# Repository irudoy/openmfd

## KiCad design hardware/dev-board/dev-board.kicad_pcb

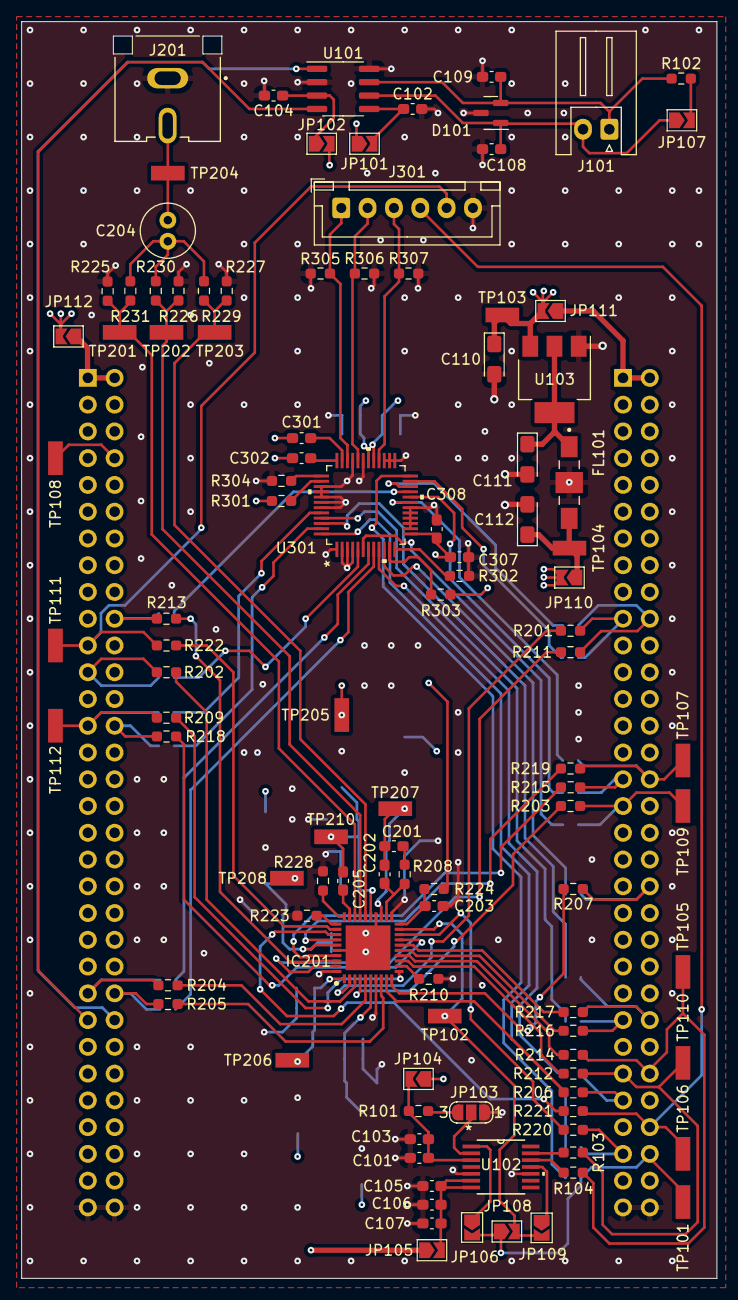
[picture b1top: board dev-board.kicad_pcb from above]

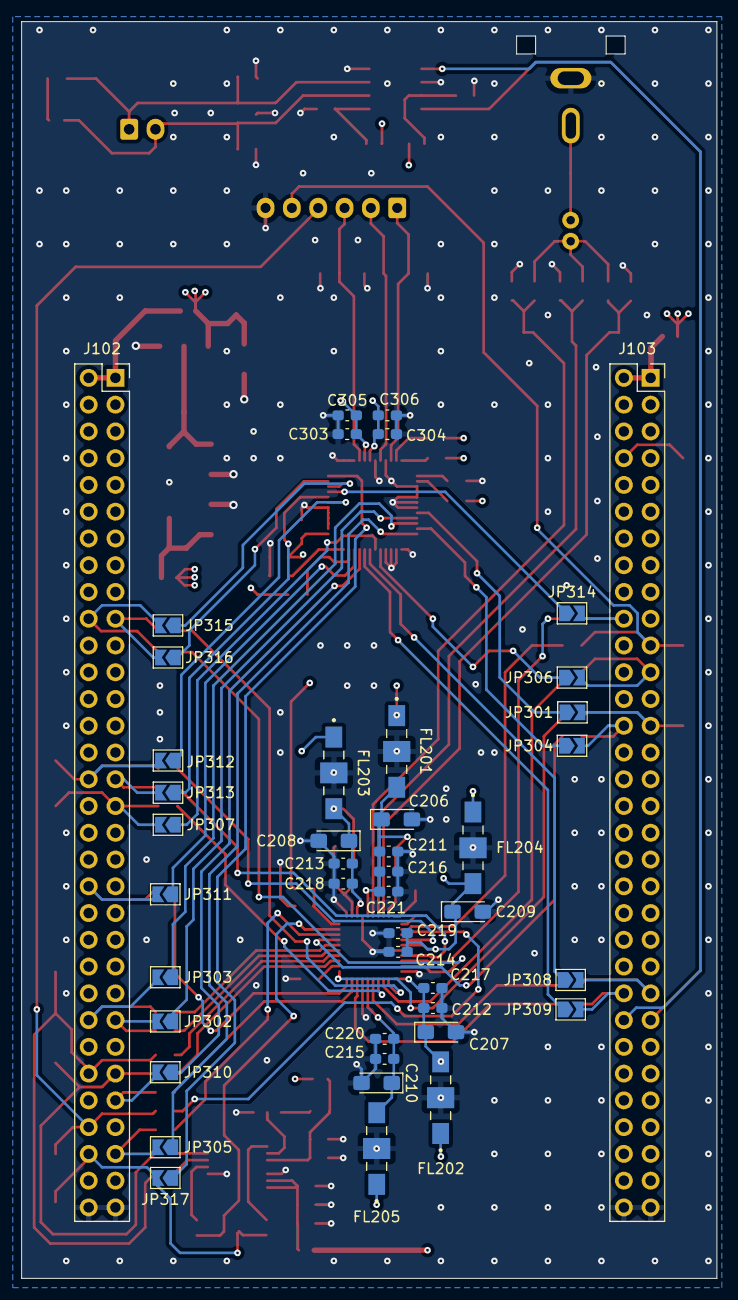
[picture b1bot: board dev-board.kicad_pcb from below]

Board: 4 copper layers, 66.0 x 119.3 mm, 150 parts (44 on the bottom side), 109 nets.

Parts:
C101, C102, C104, C105, C106, C203, C211, C212, C213, C214, C215: 100n; C_0603_1608Metric_Pad1.08x0.95mm_HandSolder
C103, C107, C221: 1u; C_0603_1608Metric_Pad1.08x0.95mm_HandSolder
C108, C109: 47p; C_0603_1608Metric_Pad1.08x0.95mm_HandSolder
C110: 10u; CP_EIA-3216-18_Kemet-A_Pad1.58x1.35mm_HandSolder
C111: 22u; CP_EIA-3216-18_Kemet-A_Pad1.58x1.35mm_HandSolder
C112, C206, C207, C208, C209, C210: 33u; CP_EIA-3216-18_Kemet-A_Pad1.58x1.35mm_HandSolder
C201: 150n; C_0603_1608Metric_Pad1.08x0.95mm_HandSolder
C202: 12n; C_0603_1608Metric_Pad1.08x0.95mm_HandSolder
C204: 220uf; C_Radial_D5.0mm_H11.0mm_P2.00mm
C205: 2n2; C_0603_1608Metric_Pad1.08x0.95mm_HandSolder
C216, C217, C218, C219, C220: 10n; C_0603_1608Metric_Pad1.08x0.95mm_HandSolder
C301, C302, C303, C304, C307: 100nf; C_0603_1608Metric_Pad1.08x0.95mm_HandSolder
C305, C306, C308: 10nf; C_0603_1608Metric_Pad1.08x0.95mm_HandSolder
D101: ESDCAN24-2BLY; SOT-23
FL101, FL201, FL202, FL203, FL204, FL205: Filter_EMI_LCL; FIL_NFE61PT472C1H9L
IC201: ADV7393BCPZ; QFN50P600X600X80-41N
J101: Conn_01x02_Pin; JST_XH_S2B-XH-A_1x02_P2.50mm_Horizontal
J102: DISC1-P1; PinSocket_2x32_P2.54mm_Vertical
J103: DISC1-P2; PinSocket_2x32_P2.54mm_Vertical
J201: CVBS; CUI_RCJ-044
J301: Connector RGB; JST_XH_B6B-XH-A_1x06_P2.50mm_Vertical
JP101, JP102, JP104, JP105, JP106, JP107, JP108, JP109, JP110, JP111, JP112, JP301, JP302, JP303, JP304, JP305, JP306, JP307, JP308, JP309, JP310, JP311, JP312, JP313, JP314, JP315, JP316, JP317: SolderJumper_2_Open; SolderJumper-2_P1.3mm_Open_TrianglePad1.0x1.5mm
JP103: SolderJumper_3_Open; SolderJumper-3_P1.3mm_Open_RoundedPad1.0x1.5mm_NumberLabels
R101, R223, R229, R230, R231: 0Ω; R_0603_1608Metric_Pad0.98x0.95mm_HandSolder
R102: 120; R_0603_1608Metric_Pad0.98x0.95mm_HandSolder
R103, R104, R201, R202, R203, R204, R205, R206, R207, R209, R210, R211, R212, R213, R214, R215, R216, R217, R218, R219, R220, R221, R222: 0; R_0603_1608Metric_Pad0.98x0.95mm_HandSolder
R208: 170 (169); R_0603_1608Metric_Pad0.98x0.95mm_HandSolder
R224: 10K; R_0603_1608Metric_Pad0.98x0.95mm_HandSolder
R225, R226, R227, R305, R306, R307: 75; R_0603_1608Metric_Pad0.98x0.95mm_HandSolder
R228: 510 1%; R_0603_1608Metric_Pad0.98x0.95mm_HandSolder
R301, R303: 4K7; R_0603_1608Metric_Pad0.98x0.95mm_HandSolder
R302: 1K; R_0603_1608Metric_Pad0.98x0.95mm_HandSolder
R304: 560; R_0603_1608Metric_Pad0.98x0.95mm_HandSolder
TP101, TP102, TP103, TP104, TP105, TP106, TP107, TP108, TP109, TP110, TP111, TP112, TP201, TP202, TP203, TP204, TP205, TP206, TP207, TP208, TP210: TestPoint_Flag; KEYSTONE_5015
U101: MCP2562-E-SN; SOIC-8_3.9x4.9mm_P1.27mm
U102: CDCE913PW; PW14
U103: AMS1117-1.8; SOT-223-3_TabPin2
U301: ADV7125KSTZ140

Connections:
+1V8: FL203.1, FL204.1, FL205.1, JP104.1 (A), JP110.2 (B)
+1V8_I: C101.1, C103.1, JP104.2 (B), R101.1, U102.3 (VDD)
+3V3: FL201.1, FL202.1, JP101.1 (A), JP105.1 (A), JP112.2 (B), R224.2, TP205.1
+3V3_C: C102.1, JP101.2 (B), U101.5 (Vio)
+3V3_I: C105.1, C106.1, C107.1, JP105.2 (B), U102.6 (VDDOUT), U102.7 (VDDOUT)
+3V3_IN: J103.1 (3V3), J103.2 (3V3), JP112.1 (A)
+5V: C110.1, C301.2, C302.2, C303.2, C304.2, C305.2, C306.2, C307.2, C308.2, JP102.2 (B), JP111.2 (B), R301.2, R303.2, TP103.1, U103.3 (VI), U301.13 (VAA), U301.29 (VAA), U301.30 (VAA)
+5V_C: C104.1, JP102.1 (A), U101.3 (VDD)
+5V_IN: J102.1 (5V), J102.2 (5V), JP111.1 (A)
/CANH: C109.1, D101.2 (K), J101.1, R102.1, U101.7 (CANH)
/CANL: C108.2, D101.1 (K), J101.2, JP107.1 (A), U101.6 (CANL)
ADV7_B3: JP312.1 (A), U301.19 (B3)
ADV7_B4: JP313.1 (A), U301.20 (B4)
ADV7_B5: JP314.1 (A), U301.21 (B5)
ADV7_B6: JP315.1 (A), U301.22 (B6)
ADV7_B7: JP316.1 (A), U301.23 (B7)
ADV7_CLK: JP317.1 (A), U301.24 (CLOCK)
ADV7_G2: JP306.1 (A), U301.5 (G2)
ADV7_G3: JP307.1 (A), U301.6 (G3)
ADV7_G4: JP308.1 (A), U301.7 (G4)
ADV7_G5: JP309.1 (A), U301.8 (G5)
ADV7_G6: JP310.1 (A), U301.9 (G6)
ADV7_G7: JP311.1 (A), U301.10 (G7)
ADV7_IOB: J301.3, R307.1, U301.28 (IOB)
ADV7_IOG: J301.2, R306.1, U301.32 (IOG)
ADV7_IOR: J301.1, R305.1, U301.34 (IOR)
ADV7_R3: JP301.1 (A), U301.44 (R3)
ADV7_R4: JP302.1 (A), U301.45 (R4)
ADV7_R5: JP303.1 (A), U301.46 (R5)
ADV7_R6: JP304.1 (A), U301.47 (R6)
ADV7_R7: JP305.1 (A), U301.48 (R7)
ADV_CLKIN: IC201.19 (CLKIN), JP108.2 (B), JP109.2 (B), TP102.1
ADV_COMP: C205.2, IC201.29 (COMP)
ADV_RSET: IC201.30 (RSET), R228.2
AVDD_3V3: C205.1, C206.1, C211.1, C216.1, C221.1, FL201.3, IC201.25 (VAA), TP210.1
CAN_RX: J103.49 (PB12), U101.4 (RXD)
CAN_TX: J103.50 (PB13), U101.1 (TXD)
DAC_1: IC201.28 (DAC_1), R225.2, R231.2, TP201.1
DAC_2: IC201.27 (DAC_2), R226.2, R230.2, TP202.1
DAC_3: IC201.26 (DAC_3), R227.2, R229.2, TP203.1
DVDD_1V8_1: C210.1, C215.1, C220.1, FL205.3, IC201.6 (VDD_1)
DVDD_1V8_2: C209.1, C214.1, C219.1, FL204.3, IC201.35 (VDD_2), TP208.1
DVDD_IO_3V3: C207.1, C212.1, C217.1, FL202.3, IC201.1 (VDD_IO), TP206.1
EXT_LF: C202.2, IC201.22 (EXT_LF), R208.1
GND: C101.2, C102.2, C103.2, C104.2, C105.2, C106.2, C107.2, C108.1, C109.2, C110.2, C111.2, C112.2, C203.2, C206.2, C207.2, C208.2, C209.2, C210.2, C211.2, C212.2, C213.2, C214.2, C215.2, C216.2, C217.2, C218.2, C219.2, C220.2, C221.2, C303.1, C304.1, C305.1, C306.1, C307.1, C308.1, D101.3 (A), FL101.2, FL201.2, FL202.2, FL203.2, FL204.2, FL205.2, IC201.7 (DGND_1), IC201.21 (PGND), IC201.24 (AGND_1), IC201.36 (DGND_2), IC201.40 (GND_IO), IC201.41 (AGND_2), J102.63 (GND), J102.64 (GND), J103.63 (GND), J103.64 (GND), J201.2 (Ext), J301.6, JP103.1 (A), R210.1, R223.1, R225.1, R226.1, R227.1, R228.1, R302.2, R304.2, R305.2, R306.2, R307.2, U101.2 (VSS), U101.8 (STBY), U102.5 (GND), U102.10 (GND), U103.1 (GND), U301.1 (GND), U301.2 (GND), U301.3 (G0), U301.4 (G1), U301.14 (GND), U301.15 (GND), U301.16 (B0), U301.17 (B1), U301.18 (B2), U301.25 (GND), U301.26 (GND), U301.27 (IOB*), U301.31 (IOG*), U301.33 (IOR*), U301.39 (GND), U301.40 (GND), U301.41 (R0), U301.42 (R1), U301.43 (R2)
I2C_SCL: J102.54 (PA8), R104.1, R214.1, TP105.1
I2C_SDA: J102.53 (PC9), R103.1, R212.1, TP110.1
LTDC_B3: J102.32 (PG11), JP312.2 (B), R219.2, TP107.1
LTDC_B4: J102.31 (PG12), JP313.2 (B), R215.2
LTDC_B5: J103.20 (PA3), JP314.2 (B), R213.2
LTDC_B6: J102.20 (PB8), JP315.2 (B), R211.2
LTDC_B7: J102.19 (PB9), JP316.2 (B), R201.1
LTDC_CLK: J102.60 (PG7), JP106.2 (B), JP108.1 (A), JP317.2 (B), TP101.1
LTDC_DE: J103.8 (PF10), TP108.1
LTDC_G2: J103.23 (PA6), JP306.2 (B), R202.1
LTDC_G3: J102.33 (PG10), JP307.2 (B), R203.1, TP109.1
LTDC_G4: J103.47 (PB10), JP308.2 (B), R204.1
LTDC_G5: J103.48 (PB11), JP309.2 (B), R205.1
LTDC_G6: J102.55 (PC7), JP310.2 (B), R206.1
LTDC_G7: J102.40 (PD3), JP311.2 (B), R207.1
LTDC_HSYNC: J102.58 (PC6), J301.4, R221.2, TP106.1
LTDC_R3: J103.27 (PB0), JP301.2 (B), R209.1, TP112.1
LTDC_R4: J102.49 (PA11), JP302.2 (B), R216.1
LTDC_R5: J102.50 (PA12), JP303.2 (B), R217.1
LTDC_R6: J103.28 (PB1), JP304.2 (B), R218.1
LTDC_R7: J102.59 (PG6), JP305.2 (B), R220.1
LTDC_VSYNC: J103.21 (PA4), J301.5, R222.2, TP111.1
unnamed: C201.2, R208.2
unnamed: C204.1, R229.1, R230.1, R231.1
unnamed: IC201.12 (ALSB), R210.2
unnamed: IC201.34 (P0), R219.1
unnamed: IC201.37 (P1), R215.1
unnamed: IC201.38 (P2), R213.1
unnamed: IC201.39 (P3), R211.1
unnamed: IC201.2 (P4), R201.2
unnamed: IC201.3 (P5), R202.2
unnamed: IC201.4 (P6), R203.2
unnamed: IC201.5 (P7), R204.2
unnamed: IC201.8, R205.2
unnamed: IC201.9, R206.2
unnamed: IC201.10, R207.2
unnamed: IC201.11, R209.2
unnamed: IC201.15 (P12), R216.2
unnamed: IC201.16 (P13), R217.2
unnamed: IC201.17 (P14), R218.2
unnamed: IC201.18 (P15), R220.2
unnamed: IC201.14 (SCL), R214.2
unnamed: IC201.13 (SDA), R212.2
unnamed: IC201.33 (~HSYNC), R221.1
unnamed: C203.1, IC201.20 (~RESET), R224.1
unnamed: IC201.32 (~VSYNC), R222.1
unnamed: C204.2, J201.1 (In), TP204.1
unnamed: JP103.3 (B), R101.2
unnamed: JP103.2 (C), U102.2 (S0)
unnamed: JP106.1 (A), U102.1 (XIN/CLK)
unnamed: JP107.2 (B), R102.2
unnamed: JP109.1 (A), U102.11 (Y1)
unnamed: C112.1, FL101.3, JP110.1 (A), TP104.1
unnamed: R103.2, U102.13 (S1/SDA)
unnamed: R104.2, U102.12 (S2/SCL)
unnamed: C111.1, FL101.1, U103.2 (VO)
unnamed: R303.1, U301.11 (BLANK*)
unnamed: C301.1, U301.35 (COMP)
unnamed: R301.1, U301.38 (PSAVE*)
unnamed: R304.1, U301.37 (RSET)
unnamed: R302.1, U301.12 (SYNC*)
unnamed: C302.1, U301.36 (VREF)
PVDD_1V8: C201.1, C202.1, C208.1, C213.1, C218.1, FL203.3, IC201.23 (PVDD), TP207.1
SFL: IC201.31 (SFL), R223.2

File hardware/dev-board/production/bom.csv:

Designator,Footprint,Quantity,Value,LCSC Part #
"C101, C102, C104, C105, C106, C203, C211, C212, C213, C214, C215",0603,11,100n,C14663
"C103, C107, C221",0603,3,1u,C14663
"C108, C109",0603,2,47p,C94904
C110,CP_EIA-3216-18_Kemet-A_Pad1.58x1.35mm_HandSolder,1,10u,
C111,CP_EIA-3216-18_Kemet-A_Pad1.58x1.35mm_HandSolder,1,22u,
"C112, C206, C207, C208, C209, C210",CP_EIA-3216-18_Kemet-A_Pad1.58x1.35mm_HandSolder,6,33u,
C201,0603,1,150n,C14663
C202,0603,1,12n,C14663
C204,C_Radial_D5.0mm_H11.0mm_P2.00mm,1,220uf,
C205,0603,1,2n2,C14663
"C216, C217, C218, C219, C220",0603,5,10n,C14663
"C301, C302, C303, C304, C307",0603,5,100nf,
"C305, C306, C308",0603,3,10nf,
D101,SOT-23,1,ESDCAN24-2BLY,C2937021
"FL101, FL201, FL202, FL203, FL204, FL205",FIL_NFE61PT472C1H9L,6,Filter_EMI_LCL,
IC201,QFN50P600X600X80-41N,1,ADV7393BCPZ,
J102,PinSocket_2x32_P2.54mm_Vertical,1,DISC1-P1,
J103,PinSocket_2x32_P2.54mm_Vertical,1,DISC1-P2,
J201,CUI_RCJ-044,1,CVBS,
J301,JST_XH_B6B-XH-A_1x06_P2.50mm_Vertical,1,Connector RGB,
JP103,SolderJumper-3_P1.3mm_Open_RoundedPad1.0x1.5mm_NumberLabels,1,SolderJumper_3_Open,
R101,0603,1,0Ω,
R102,0603,1,120,C22787
"R103, R104, R201, R202, R203, R204, R205, R206, R207, R209, R210, R211, R212, R213, R214, R215, R216, R217, R218, R219, R220, R221, R222",0603,23,0,
R208,0603,1,170 (169),C22787
"R223, R229, R230, R231",0603,4,0Ω,C22787
R224,0603,1,10K,C22787
"R225, R226, R227",0603,3,75,C22787
R228,0603,1,510 1%,C22787
"R301, R303",0603,2,4K7,
R302,0603,1,1K,
R304,0603,1,560,
"R305, R306, R307",0603,3,75,
"TP101, TP102, TP103, TP104, TP105, TP106, TP107, TP108, TP109, TP110, TP111, TP112, TP201, TP202, TP203, TP204, TP205, TP206, TP207, TP208, TP210",KEYSTONE_5015,21,TestPoint_Flag,
U101,SOIC-8_3.9x4.9mm_P1.27mm,1,MCP2562-E-SN,C53609
U102,PW14,1,CDCE913PW,
U103,SOT-223-3_TabPin2,1,AMS1117-1.8,
U301,ADV7125KSTZ140,1,ADV7125KSTZ140,

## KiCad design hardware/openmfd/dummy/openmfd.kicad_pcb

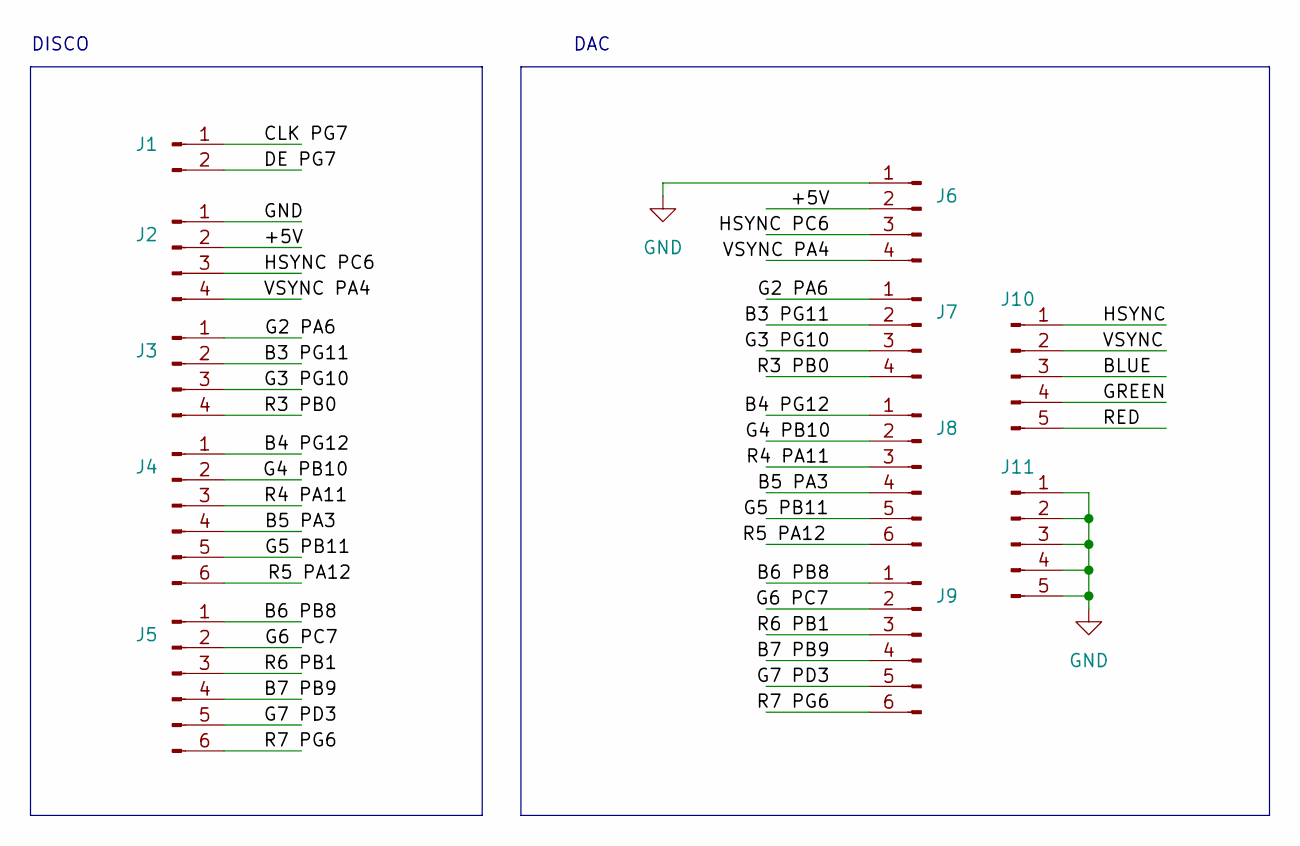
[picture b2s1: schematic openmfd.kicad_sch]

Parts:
J1: Conn_01x02_Male; JST_XH_B2B-XH-A_1x02_P2.50mm_Vertical
J2, J3, J6, J7: Conn_01x04_Male; JST_XH_B4B-XH-A_1x04_P2.50mm_Vertical
J4, J5, J8, J9: Conn_01x06_Male; JST_XH_B6B-XH-A_1x06_P2.50mm_Vertical
J10, J11: Conn_01x05_Male; JST_XH_B5B-XH-A_1x05_P2.50mm_Vertical

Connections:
/+5V: J2.2, J6.2
/B3 PG11: J3.2, J7.2
/B4 PG12: J4.1, J8.1
/B5 PA3: J4.4, J8.4
/B6 PB8: J5.1, J9.1
/B7 PB9: J5.4, J9.4
/BLUE: J10.3
/CLK PG7: J1.1
/DE PG7: J1.2
/G2 PA6: J3.1, J7.1
/G3 PG10: J3.3, J7.3
/G4 PB10: J4.2, J8.2
/G5 PB11: J4.5, J8.5
/G6 PC7: J5.2, J9.2
/G7 PD3: J5.5, J9.5
/GREEN: J10.4
/HSYNC: J10.1
/HSYNC PC6: J2.3, J6.3
/R3 PB0: J3.4, J7.4
/R4 PA11: J4.3, J8.3
/R5 PA12: J4.6, J8.6
/R6 PB1: J5.3, J9.3
/R7 PG6: J5.6, J9.6
/RED: J10.5
/VSYNC: J10.2
/VSYNC PA4: J2.4, J6.4
GND: J2.1, J6.1, J11.1, J11.2, J11.3, J11.4, J11.5

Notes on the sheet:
DAC
DISCO

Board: 2 copper layers, 11 parts (0 on the bottom side), 20 nets, no tracks yet.

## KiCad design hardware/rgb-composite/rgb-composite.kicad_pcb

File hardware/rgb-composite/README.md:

### The reason why AD724 is not suitable for this application

From datasheet:

> The AD724 can be used to convert the analog RGB output from a personal computer’s VGA card to the NTSC or PAL television standards. To accomplish this it is important to understand that the AD724 **requires interlaced RGB video** and clock rates that are consistent with those required by the television standards.

That's the case. STM32 LTDC can't output INTERLACED video signal.

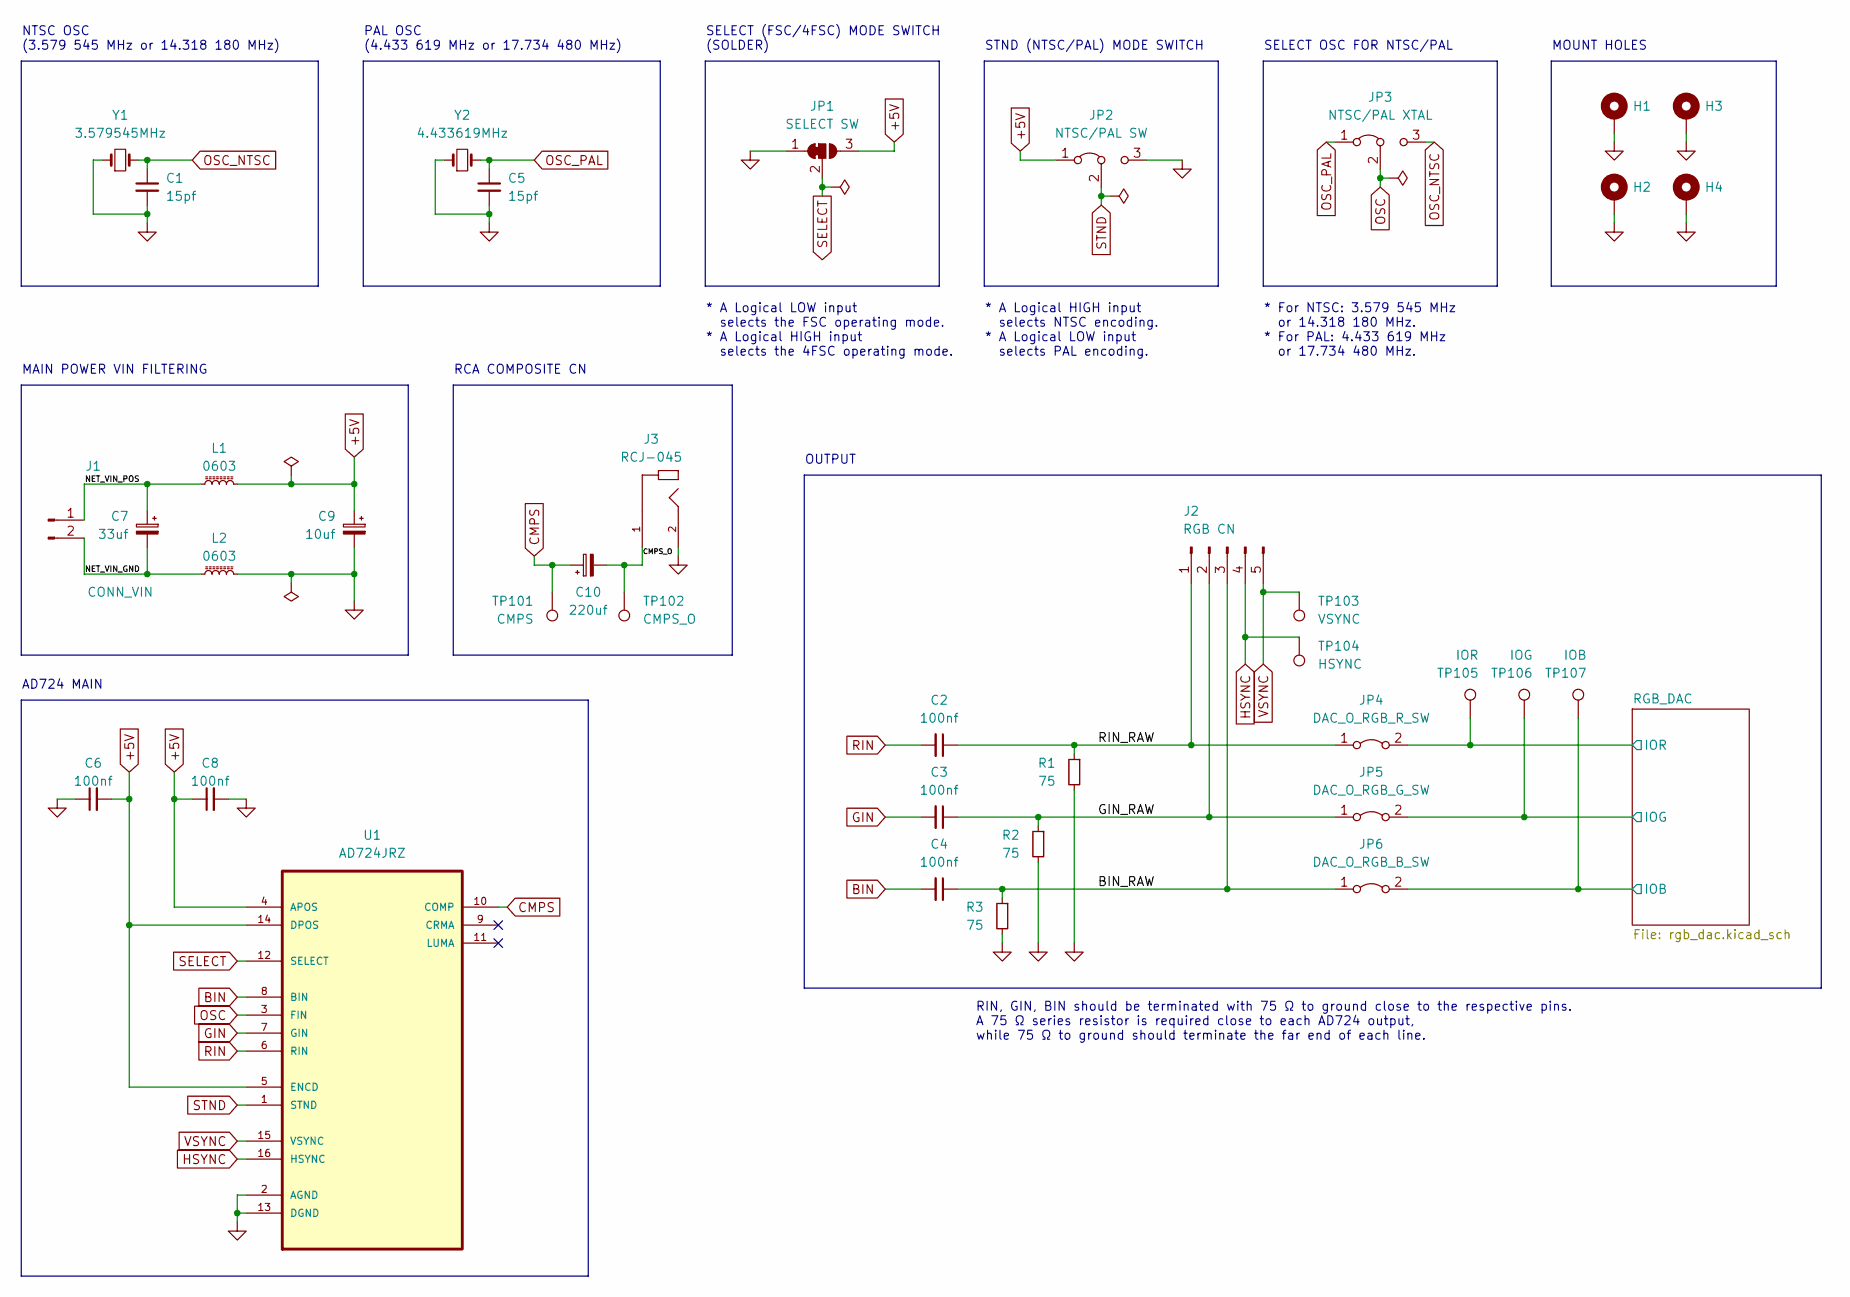
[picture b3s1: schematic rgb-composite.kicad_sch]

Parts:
C1, C5: 15pf; C_0603_1608Metric_Pad1.08x0.95mm_HandSolder
C2, C3, C4, C6, C8: 100nf; C_0603_1608Metric_Pad1.08x0.95mm_HandSolder
C7: 33uf; CP_EIA-3528-21_Kemet-B_Pad1.50x2.35mm_HandSolder
C9: 10uf; CP_EIA-3216-18_Kemet-A_Pad1.58x1.35mm_HandSolder
C10: 220uf; C_Radial_D5.0mm_H11.0mm_P2.00mm
H1, H2, H3, H4: MountingHole_Pad; MountingHole_3.2mm_M3_Pad_Via
J1: CONN_VIN; JST_XH_B2B-XH-A_1x02_P2.50mm_Vertical
J2: RGB CN; JST_XH_B5B-XH-A_1x05_P2.50mm_Vertical
J3: RCJ-045; CUI_RCJ-JP
JP1: SELECT SW; SolderJumper-3_P1.3mm_Open_RoundedPad1.0x1.5mm
JP2: NTSC/PAL SW; PinHeader_1x03_P2.54mm_Vertical
JP3: NTSC/PAL XTAL; PinHeader_1x03_P2.54mm_Vertical
JP4: DAC_O_RGB_R_SW; PinHeader_1x02_P2.54mm_Vertical
JP5: DAC_O_RGB_G_SW; PinHeader_1x02_P2.54mm_Vertical
JP6: DAC_O_RGB_B_SW; PinHeader_1x02_P2.54mm_Vertical
L1, L2: 0603; L_0603_1608Metric_Pad1.05x0.95mm_HandSolder
R1, R2, R3: 75; R_0603_1608Metric_Pad0.98x0.95mm_HandSolder
TP101: CMPS; TestPoint_Loop_D2.60mm_Drill0.9mm_Beaded
TP102: CMPS_O; TestPoint_Loop_D2.60mm_Drill0.9mm_Beaded
TP103: VSYNC; TestPoint_Loop_D2.60mm_Drill0.9mm_Beaded
TP104: HSYNC; TestPoint_Loop_D2.60mm_Drill0.9mm_Beaded
TP105: IOR; TestPoint_Loop_D2.60mm_Drill0.9mm_Beaded
TP106: IOG; TestPoint_Loop_D2.60mm_Drill0.9mm_Beaded
TP107: IOB; TestPoint_Loop_D2.60mm_Drill0.9mm_Beaded
U1: AD724JRZ; SOIC127P1032X265-16N; MPN AD724JRZ
Y1: 3.579545MHz; Crystal_HC49-4H_Vertical
Y2: 4.433619MHz; Crystal_HC49-U_Vertical

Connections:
+5V: C6.2, C8.1, C9.1, JP1.3 (B), JP2.1 (A), L1.1, U1.4 (APOS), U1.5 (ENCD), U1.14 (DPOS); also elsewhere on the board
/BIN_RAW: C4.1, J2.3, JP6.1 (A), R3.1
/CMPS_O: C10.2, J3.1, TP102.1
/GIN_RAW: C3.1, J2.2, JP5.1 (A), R2.1
/NET_VIN_GND: C7.2, J1.2, L2.2
/NET_VIN_POS: C7.1, J1.1, L1.2
/RIN_RAW: C2.1, J2.1, JP4.1 (A), R1.1
BIN: C4.2, U1.8 (BIN)
CMPS: C10.1, TP101.1, U1.10 (COMP)
GIN: C3.2, U1.7 (GIN)
GND: C1.2, C5.2, C6.1, C8.2, C9.2, H1.1, H2.1, H3.1, H4.1, J3.2, JP1.1 (A), JP2.3 (B), L2.1, R1.2, R2.2, R3.2, U1.2 (AGND), U1.13 (DGND), Y1.1, Y2.1; also elsewhere on the board
HSYNC: J2.4, TP104.1, U1.16 (HSYNC)
IOB: JP6.2 (B), TP107.1; also elsewhere on the board
IOG: JP5.2 (B), TP106.1; also elsewhere on the board
IOR: JP4.2 (B), TP105.1; also elsewhere on the board
OSC: JP3.2 (C), U1.3 (FIN)
OSC_NTSC: C1.1, JP3.3 (B), Y1.2
OSC_PAL: C5.1, JP3.1 (A), Y2.2
RIN: C2.2, U1.6 (RIN)
SELECT: JP1.2 (C), U1.12 (SELECT)
STND: JP2.2 (C), U1.1 (STND)
VSYNC: J2.5, TP103.1, U1.15 (VSYNC)

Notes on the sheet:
OUTPUT
* For NTSC: 3.579 545 MHz or 14.318 180 MHz. * For PAL: 4.433 619 MHz or 17.734 480 MHz.
SELECT (FSC/4FSC) MODE SWITCH (SOLDER)
AD724 MAIN
* A Logical HIGH input selects NTSC encoding. * A Logical LOW input selects PAL encoding.
RCA COMPOSITE CN
SELECT OSC FOR NTSC/PAL
NTSC OSC (3.579 545 MHz or 14.318 180 MHz)
MOUNT HOLES
PAL OSC (4.433 619 MHz or 17.734 480 MHz)
* A Logical LOW input selects the FSC operating mode. * A Logical HIGH input selects the 4FSC operating mode.
RIN, GIN, BIN should be terminated with 75 Ω to ground close to the respective pins. A 75 Ω series resistor is required close to each AD724 output, while 75 Ω to ground should terminate the far end of each line.
MAIN POWER VIN FILTERING
STND (NTSC/PAL) MODE SWITCH

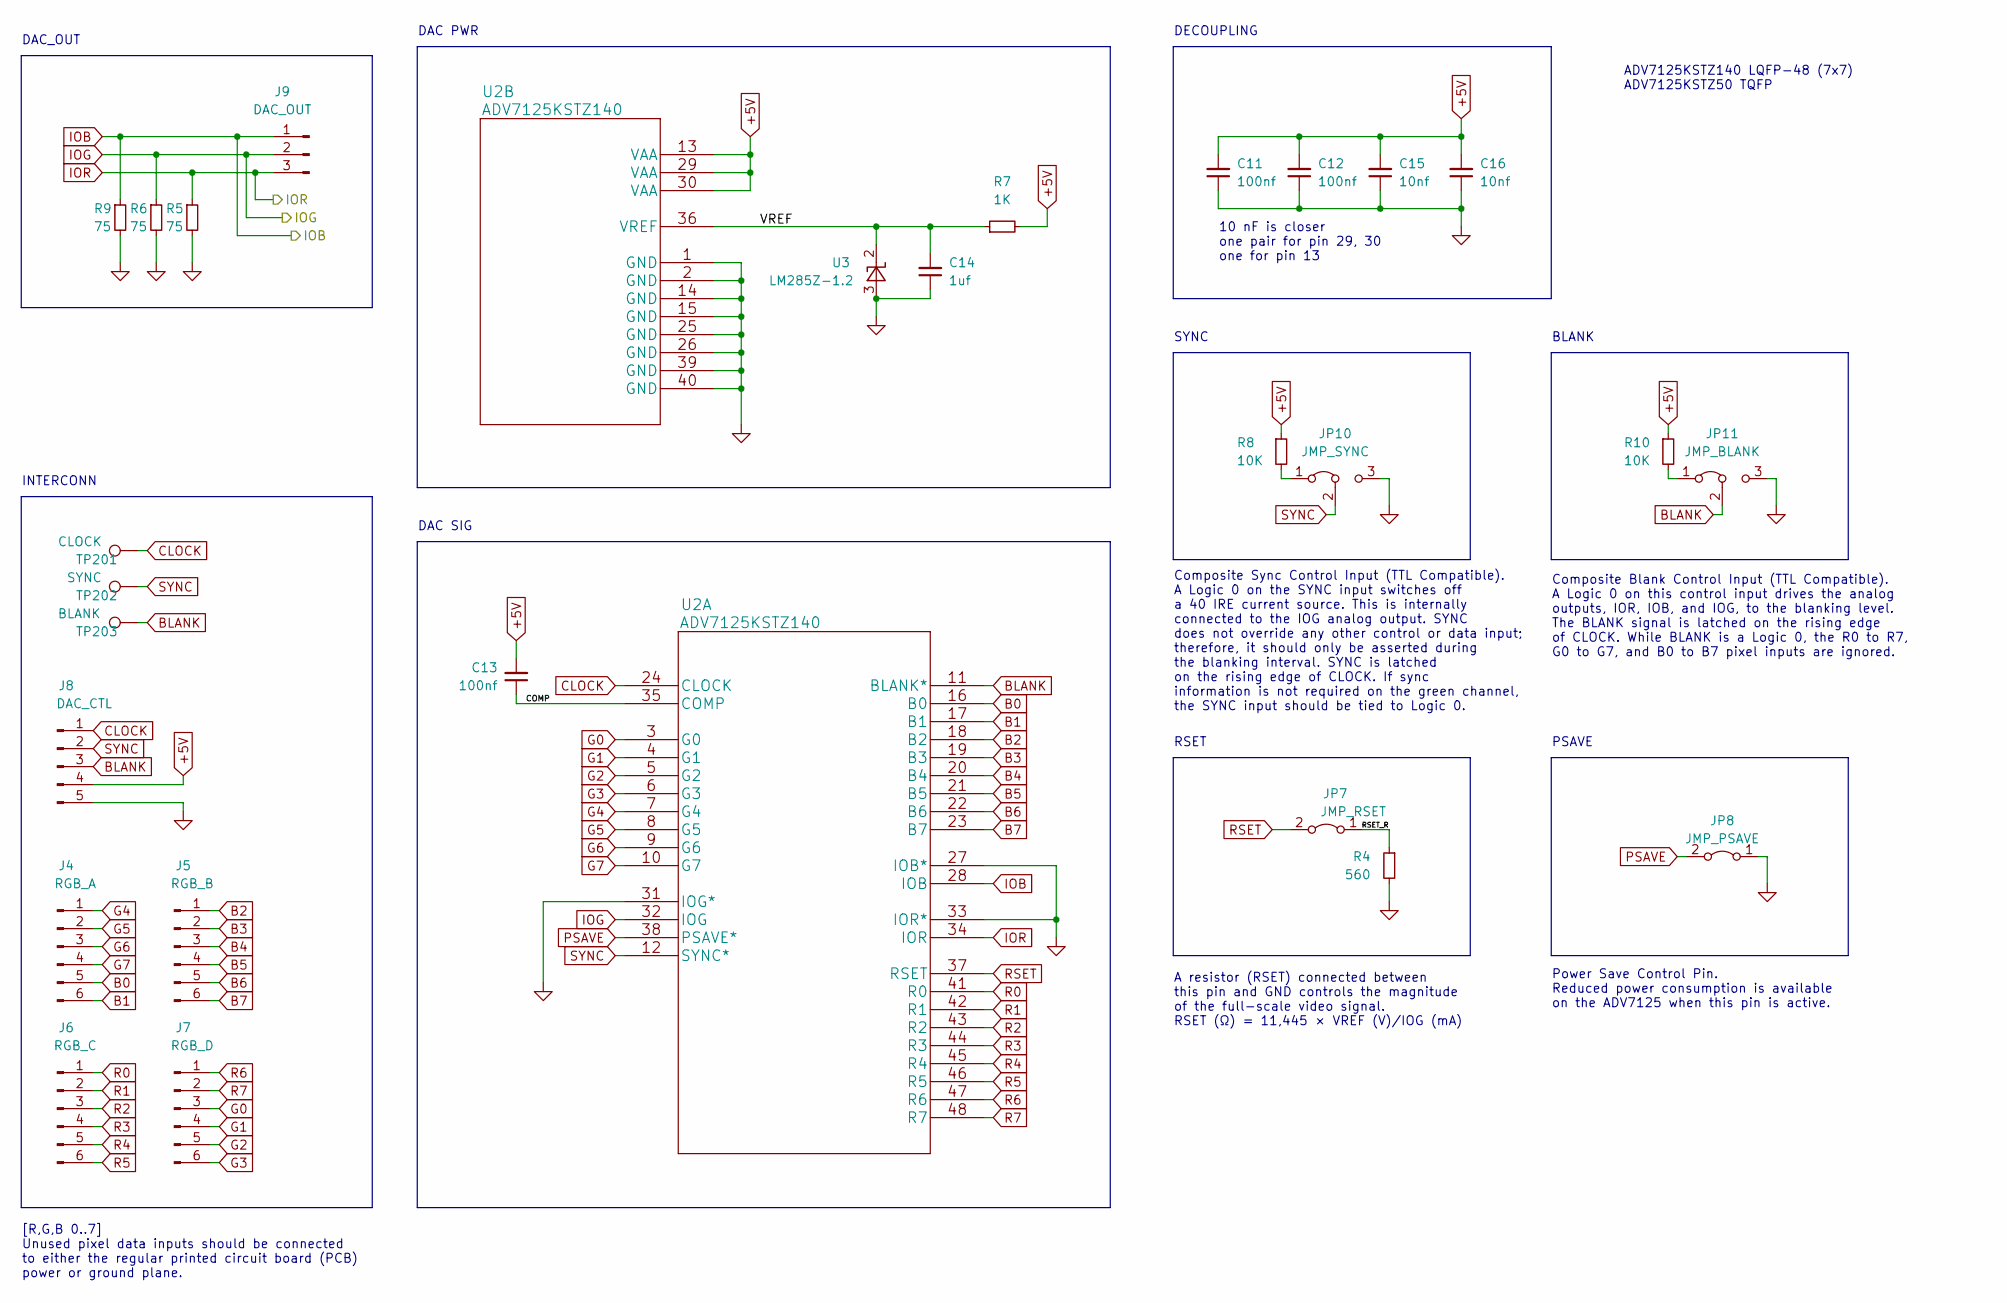
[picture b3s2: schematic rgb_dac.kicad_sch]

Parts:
C11, C12, C13: 100nf; C_0603_1608Metric_Pad1.08x0.95mm_HandSolder
C14: 1uf; C_0603_1608Metric_Pad1.08x0.95mm_HandSolder
C15, C16: 10nf; C_0603_1608Metric_Pad1.08x0.95mm_HandSolder
J4: RGB_A; JST_XH_B6B-XH-A_1x06_P2.50mm_Vertical
J5: RGB_B; JST_XH_B6B-XH-A_1x06_P2.50mm_Vertical
J6: RGB_C; JST_XH_B6B-XH-A_1x06_P2.50mm_Vertical
J7: RGB_D; JST_XH_B6B-XH-A_1x06_P2.50mm_Vertical
J8: DAC_CTL; JST_XH_B5B-XH-A_1x05_P2.50mm_Vertical
J9: DAC_OUT; JST_XH_B3B-XH-A_1x03_P2.50mm_Vertical
JP7: JMP_RSET; PinHeader_1x02_P2.54mm_Vertical
JP8: JMP_PSAVE; PinHeader_1x02_P2.54mm_Vertical
JP10: JMP_SYNC; PinHeader_1x03_P2.54mm_Vertical
JP11: JMP_BLANK; PinHeader_1x03_P2.54mm_Vertical
R4: 560; R_0603_1608Metric_Pad0.98x0.95mm_HandSolder
R5, R6, R9: 75; R_0603_1608Metric_Pad0.98x0.95mm_HandSolder
R7: 1K; R_0603_1608Metric_Pad0.98x0.95mm_HandSolder
R8, R10: 10K; R_0603_1608Metric_Pad0.98x0.95mm_HandSolder
TP201: CLOCK; TestPoint_Loop_D2.60mm_Drill0.9mm_Beaded
TP202: SYNC; TestPoint_Loop_D2.60mm_Drill0.9mm_Beaded
TP203: BLANK; TestPoint_Loop_D2.60mm_Drill0.9mm_Beaded
U2: ADV7125KSTZ140
U3: LM285Z-1.2; TO-92_Inline

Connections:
+5V: C11.2, C12.2, C13.2, C15.2, C16.2, J8.4, R7.2, R8.1, R10.1, U2.13 (VAA), U2.29 (VAA), U2.30 (VAA); also elsewhere on the board
/RGB_DAC/COMP: C13.1, U2.35 (COMP)
/RGB_DAC/RSET_R: JP7.1 (A), R4.1
/RGB_DAC/VREF: C14.2, R7.1, U2.36 (VREF), U3.2 (K); also elsewhere on the board
B0: J4.5, U2.16 (B0)
B1: J4.6, U2.17 (B1)
B2: J5.1, U2.18 (B2)
B3: J5.2, U2.19 (B3)
B4: J5.3, U2.20 (B4)
B5: J5.4, U2.21 (B5)
B6: J5.5, U2.22 (B6)
B7: J5.6, U2.23 (B7)
BLANK: J8.3, JP11.2 (C), TP203.1, U2.11 (BLANK*)
CLOCK: J8.1, TP201.1, U2.24 (CLOCK)
G0: J7.3, U2.3 (G0)
G1: J7.4, U2.4 (G1)
G2: J7.5, U2.5 (G2)
G3: J7.6, U2.6 (G3)
G4: J4.1, U2.7 (G4)
G5: J4.2, U2.8 (G5)
G6: J4.3, U2.9 (G6)
G7: J4.4, U2.10 (G7)
GND: C11.1, C12.1, C14.1, C15.1, C16.1, J8.5, JP8.1 (A), JP10.3 (B), JP11.3 (B), R4.2, R5.2, R6.2, R9.2, U2.1 (GND), U2.2 (GND), U2.14 (GND), U2.15 (GND), U2.25 (GND), U2.26 (GND), U2.27 (IOB*), U2.31 (IOG*), U2.33 (IOR*), U2.39 (GND), U2.40 (GND), U3.3 (A); also elsewhere on the board
IOB: J9.1, R9.1, U2.28 (IOB); also elsewhere on the board
IOG: J9.2, R6.1, U2.32 (IOG); also elsewhere on the board
IOR: J9.3, R5.1, U2.34 (IOR); also elsewhere on the board
unnamed: JP10.1 (A), R8.2
unnamed: JP11.1 (A), R10.2
PSAVE: JP8.2 (B), U2.38 (PSAVE*)
R0: J6.1, U2.41 (R0)
R1: J6.2, U2.42 (R1)
R2: J6.3, U2.43 (R2)
R3: J6.4, U2.44 (R3)
R4: J6.5, U2.45 (R4)
R5: J6.6, U2.46 (R5)
R6: J7.1, U2.47 (R6)
R7: J7.2, U2.48 (R7)
RSET: JP7.2 (B), U2.37 (RSET)
SYNC: J8.2, JP10.2 (C), TP202.1, U2.12 (SYNC*)

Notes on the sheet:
10 nF is closer one pair for pin 29, 30 one for pin 13
DECOUPLING
[R,G,B 0..7] Unused pixel data inputs should be connected to either the regular printed circuit board (PCB) power or ground plane.
RSET
DAC PWR
SYNC
DAC SIG
BLANK
PSAVE
INTERCONN
DAC_OUT
Composite Blank Control Input (TTL Compatible). A Logic 0 on this control input drives the analog outputs, IOR, IOB, and IOG, to the blanking level. The BLANK signal is latched on the rising edge of CLOCK. While BLANK is a Logic 0, the R0 to R7, G0 to G7, and B0 to B7 pixel inputs are ignored.
Power Save Control Pin. Reduced power consumption is available on the ADV7125 when this pin is active.
Composite Sync Control Input (TTL Compatible). A Logic 0 on the SYNC input switches off a 40 IRE current source. This is internally connected to the IOG analog output. SYNC does not override any other control or data input; therefore, it should only be asserted during the blanking interval. SYNC is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
A resistor (RSET) connected between this pin and GND controls the magnitude of the full-scale video signal. RSET (Ω) = 11,445 × VREF (V)/IOG (mA)
ADV7125KSTZ140 LQFP-48 (7x7) ADV7125KSTZ50 TQFP

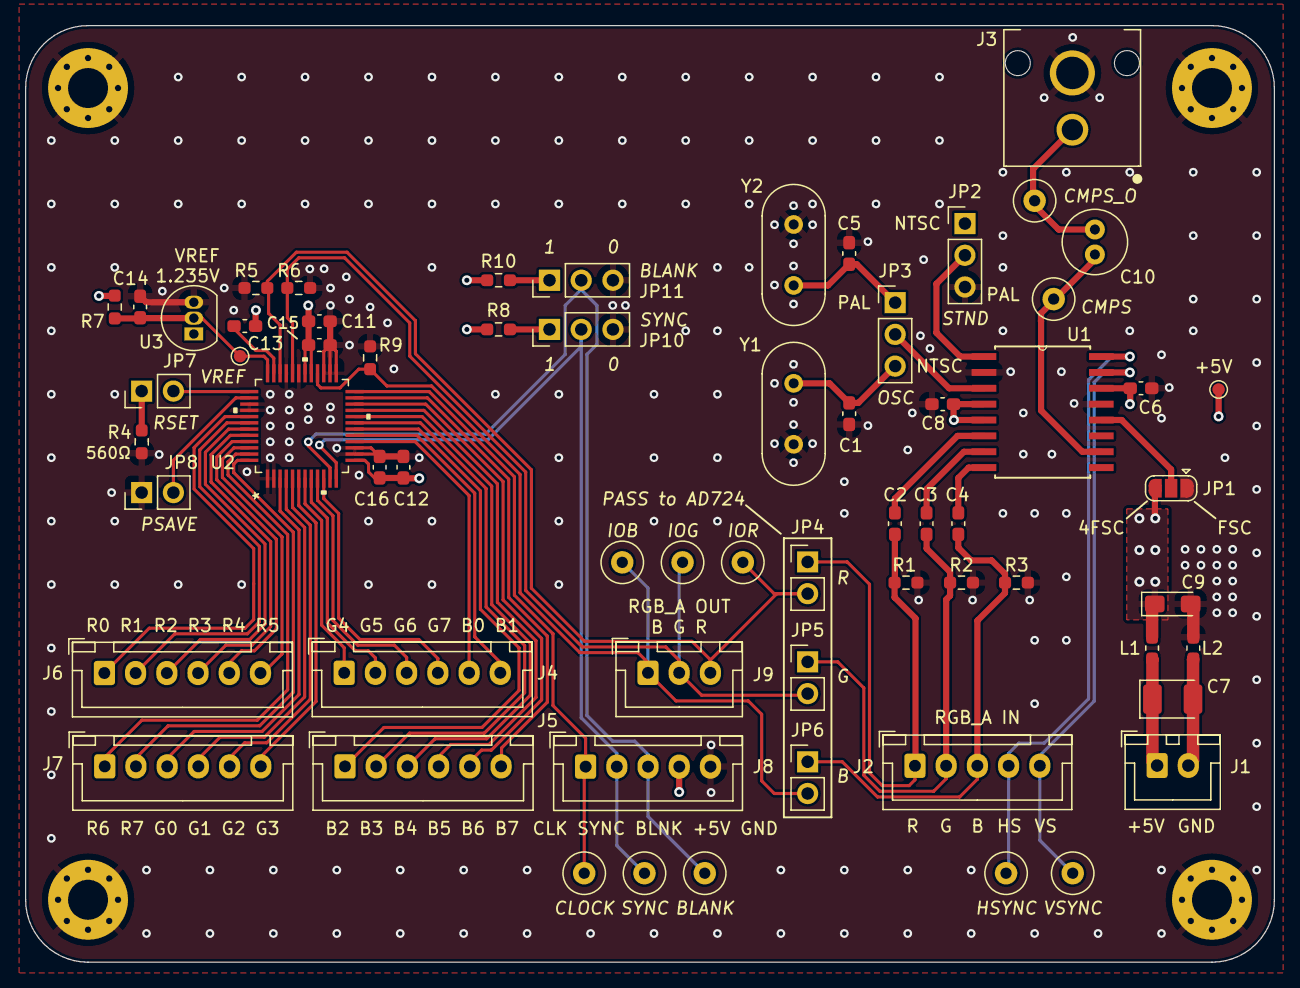
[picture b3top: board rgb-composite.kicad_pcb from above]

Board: 4 copper layers, 100.0 x 75.0 mm, 67 parts (0 on the bottom side), 56 nets.

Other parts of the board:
VREF: TestPoint_Pad_D1.0mm

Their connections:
/RGB_DAC/VREF: VREF.1; also elsewhere on the board

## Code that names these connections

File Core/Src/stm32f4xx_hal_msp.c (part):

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
    __HAL_RCC_GPIOB_CLK_ENABLE();
    /**CAN2 GPIO Configuration
    PB12     ------> CAN2_RX
    PB13     ------> CAN2_TX
    */
    GPIO_InitStruct.Pin = CAN_RX_Pin|CAN_TX_Pin;
    GPIO_InitStruct.Mode = GPIO_MODE_AF_PP;
    GPIO_InitStruct.Pull = GPIO_NOPULL;
    GPIO_InitStruct.Speed = GPIO_SPEED_FREQ_VERY_HIGH;
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    __HAL_RCC_CAN1_CLK_DISABLE();

    /**CAN2 GPIO Configuration
    PB12     ------> CAN2_RX
    PB13     ------> CAN2_TX
    */
    HAL_GPIO_DeInit(GPIOB, CAN_RX_Pin|CAN_TX_Pin);

    /* CAN2 interrupt DeInit */
    HAL_NVIC_DisableIRQ(CAN2_RX0_IRQn);
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    __HAL_RCC_GPIOC_CLK_ENABLE();
    __HAL_RCC_GPIOA_CLK_ENABLE();
    /**I2C3 GPIO Configuration
    PC9     ------> I2C3_SDA
    PA8     ------> I2C3_SCL
    */
    GPIO_InitStruct.Pin = I2C3_SDA_Pin;
    GPIO_InitStruct.Mode = GPIO_MODE_AF_OD;
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    __HAL_RCC_I2C3_CLK_DISABLE();

    /**I2C3 GPIO Configuration
    PC9     ------> I2C3_SDA
    PA8     ------> I2C3_SCL
    */
    HAL_GPIO_DeInit(I2C3_SDA_GPIO_Port, I2C3_SDA_Pin);

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    __HAL_RCC_GPIOC_CLK_ENABLE();
    __HAL_RCC_GPIOD_CLK_ENABLE();
    /**LTDC GPIO Configuration
    PF10     ------> LTDC_DE
    PA3     ------> LTDC_B5
    PA4     ------> LTDC_VSYNC
    PA6     ------> LTDC_G2
    PB0     ------> LTDC_R3
    PB1     ------> LTDC_R6
    PB10     ------> LTDC_G4
    PB11     ------> LTDC_G5
    PG6     ------> LTDC_R7
    PG7     ------> LTDC_CLK
    PC6     ------> LTDC_HSYNC
    PC7     ------> LTDC_G6
    PA11     ------> LTDC_R4
    PA12     ------> LTDC_R5
    PC10     ------> LTDC_R2
    PD3     ------> LTDC_G7
    PD6     ------> LTDC_B2
    PG10     ------> LTDC_G3
    PG11     ------> LTDC_B3
    PG12     ------> LTDC_B4
    PB8     ------> LTDC_B6
    PB9     ------> LTDC_B7
    */
    GPIO_InitStruct.Pin = ENABLE_Pin;
    GPIO_InitStruct.Mode = GPIO_MODE_AF_PP;
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    GPIO_InitStruct.Alternate = GPIO_AF14_LTDC;
    HAL_GPIO_Init(ENABLE_GPIO_Port, &GPIO_InitStruct);

    GPIO_InitStruct.Pin = B5_Pin|VSYNC_Pin;
    GPIO_InitStruct.Mode = GPIO_MODE_AF_PP;
    GPIO_InitStruct.Pull = GPIO_NOPULL;
    GPIO_InitStruct.Speed = GPIO_SPEED_FREQ_LOW;
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    GPIO_InitStruct.Alternate = GPIO_AF14_LTDC;
    HAL_GPIO_Init(GPIOG, &GPIO_InitStruct);

    GPIO_InitStruct.Pin = HSYNC_Pin|G6_Pin;
    GPIO_InitStruct.Mode = GPIO_MODE_AF_PP;
    GPIO_InitStruct.Pull = GPIO_NOPULL;
    GPIO_InitStruct.Speed = GPIO_SPEED_FREQ_VERY_HIGH;
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    __HAL_RCC_LTDC_CLK_DISABLE();

    /**LTDC GPIO Configuration
    PF10     ------> LTDC_DE
    PA3     ------> LTDC_B5
    PA4     ------> LTDC_VSYNC
    PA6     ------> LTDC_G2
    PB0     ------> LTDC_R3
    PB1     ------> LTDC_R6
    PB10     ------> LTDC_G4
    PB11     ------> LTDC_G5
    PG6     ------> LTDC_R7
    PG7     ------> LTDC_CLK
    PC6     ------> LTDC_HSYNC
    PC7     ------> LTDC_G6
    PA11     ------> LTDC_R4
    PA12     ------> LTDC_R5
    PC10     ------> LTDC_R2
    PD3     ------> LTDC_G7
    PD6     ------> LTDC_B2
    PG10     ------> LTDC_G3
    PG11     ------> LTDC_B3
    PG12     ------> LTDC_B4
    PB8     ------> LTDC_B6
    PB9     ------> LTDC_B7
    */
    HAL_GPIO_DeInit(ENABLE_GPIO_Port, ENABLE_Pin);

    HAL_GPIO_DeInit(GPIOA, B5_Pin|VSYNC_Pin|G2_Pin|R4_Pin
                          |R5_Pin);

    HAL_GPIO_DeInit(GPIOB, R3_Pin|R6_Pin|G4_Pin|G5_Pin
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    HAL_GPIO_DeInit(GPIOG, R7_Pin|DOTCLK_Pin|G3_Pin|B3_Pin
                          |B4_Pin);

    HAL_GPIO_DeInit(GPIOC, HSYNC_Pin|G6_Pin|R2_Pin);

    HAL_GPIO_DeInit(GPIOD, G7_Pin|B2_Pin);

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
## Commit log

2022-05-31 root
2022-05-31 init
2022-05-31 keep some dirs
2022-05-31 change V Sync Polarity to +
2022-05-31 add .mxproject to gitignore
2022-05-31 upd .cproject
2022-05-31 keep dir
2022-05-31 upd fonts
2022-05-31 create gauge custome container
2022-05-31 fix text align
2022-05-31 cs mnr
2022-06-01 enable ili9341 lcd
2022-06-01 add comments
2022-06-01 init debug display; use queue for HW->Model comms
2022-06-02 format
2022-06-03 set up can bus
2022-06-04 refine data format
2022-06-04 debug screen done
2022-06-04 set Pixel Clock to 4.75
2022-06-20 ignore launch config
2022-06-20 add cbus controller communication
2022-06-22 fix cbus mnr, fix minmax clt
2022-06-22 touchgfx: update fonts
2022-06-22 rework scales
2022-06-24 improve gauges
2022-06-24 ref scale types
2022-06-24 scales done
2022-06-25 gauges done
2022-06-25 switch peak/current
2022-06-25 current pos mnr
2022-06-25 redzone
2022-06-25 add afr
2022-06-26 add graph screen
2022-06-28 improve graph
2022-06-28 graph perf
2022-06-28 migrate to TouchGFX v4.20.0
2022-06-28 graph improvements
2022-06-29 graph overlay
2022-06-29 adjust ltdc timings
    https://www.epanorama.net/faq/vga2rgb/calc.html
    Modeline "320x240" 6.700 320 336 367 426 240 244 247 262 -hsync -vsync
2022-06-30 new graph bg
2022-07-01 invalidate graph label
2022-07-01 mnr ui fixes
2022-07-01 graph done
2022-07-01 add bg, ref mnr
2022-07-01 offset graph
2022-07-01 gauge: fix negative float val
2022-07-01 screen change rough implementation
2022-10-31 configure LTDC for new DAC
2022-10-31 fix HW btn controller
2022-10-31 migrate to cubemx v6.6.1
2022-11-03 change ltdc freq to 7.35
2022-11-03 adjust timings
2022-11-03 migrate height 240->234
2022-11-03 improve test screen
2022-11-03 adjust ltdc clock
2023-11-27 Create LICENSE
2023-12-15 Add renovate.json
2024-05-24 update project structure
2024-05-24 add root .gitignore
2024-05-24 add old schematics
2024-07-10 adv7393 dev-board wip
2024-07-15 adv7393 dev-board done
2024-07-24 production
2024-10-23 fix can addr
2024-10-23 generate after cube migration
2024-10-23 adjust ltdc settings
2024-10-23 adjust clock
2024-10-23 migrate cube project
2024-10-23 try 1
2024-10-24 wip conf adv7393
2025-02-26 fix devboard sch
2025-02-26 CMakeLists

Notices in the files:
Core/Src/stm32f4xx_hal_msp.c:
Copyright (c) 2022 STMicroelectronics.
All rights reserved.
This software is licensed under terms that can be found in the LICENSE file
parts and their libraries:
Copyright 2021 Accelerated Designs. All rights reserved.
